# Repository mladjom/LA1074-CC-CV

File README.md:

# LT1074 Adjustable CV/CC Bench Power Supply

A buck-derived bench power supply built around the LT1074CT1 switching regulator, with adjustable output voltage and adjustable current limiting, plus a digital voltage/current readout.

## Overview

- **Topology:** LT1074CT1 buck converter
- **Voltage control:** Adjustable via potentiometer (RV1), feeding the LT1074's FB pin
- **Current control:** Adjustable fold-back current limit via an op-amp sense/compare loop, summed into the LT1074's VC (compensation) pin
- **Reference:** TL431-based VREF (2.5V), used by both the current-set pot and the current-sense op-amp
- **Readout:** DSN-VC288 digital voltmeter/ammeter module

## Main power stage

| Component | Function |
|---|---|
| U1 – LT1074CT1 | Buck regulator (VIN pin5, VSW pin4, FB pin1, VC pin2, GND pin3) |
| L1 | Buck inductor |
| D1 – MBR745 | Catch (freewheeling) diode |
| Cin1 | Input bulk capacitor (470µF) |
| COUT | Output bulk capacitor (470µF) |
| RV1 (5K) | Output voltage adjustment — sets FB divider ratio, adjusts VOUT |
| R2 (0.1Ω) | Current-sense shunt, in the ground return path |

**Output voltage** is set by RV1, which forms the feedback divider into the LT1074's FB pin (regulated against its internal ~2.21V reference). Turning RV1 sweeps VOUT from a few hundred mV up to close to VIN.

## Current-limit loop

| Component | Function |
|---|---|
| R2 (0.1Ω) | Current-sense shunt |
| U1A (LM358) | Difference amplifier — converts the voltage across R2 into a single-ended ISENSE signal (via R3/R4) |
| RV2 (10K) | Current setpoint (ISET), derived from VREF |
| U1B (LM358) | Compares ISENSE vs ISET, output = ICONTROL |
| R5 (1K) + clamp diode | Sums ICONTROL into the LT1074's VC pin |
| C3 (10nF) | Filtering on ICONTROL |

**How it works:** Under normal operation (load current below the ISET threshold), U1B's output (ICONTROL) sits high, well above VC's normal operating range. The clamp diode between R5 and VC is wired **anode toward VC, cathode toward R5/U1B**, so it stays reverse-biased and the current loop has no effect on regulation — the LT1074 is free to run pure CV mode.

If load current exceeds the ISET threshold, ISENSE rises above ISET, U1B's output swings low — below VC's level — forward-biasing the clamp diode. This lets U1B pull VC down through R5, reducing the LT1074's duty cycle and folding back the output voltage to hold current at the ISET limit. This is a standard current fold-back scheme, not a hard/foldback-free limiter — output voltage will sag as needed to keep current at the set point.

**Diode direction matters:** the opposite orientation (cathode toward VC) permanently forward-biases the diode any time ICONTROL idles high, jamming VC upward and preventing CV regulation entirely. If voltage ever "gets stuck near VIN and won't adjust," this is the first thing to check.

## Reference and setpoint

- **U2 (TL431LP) + R6 + C4** generate VREF (~2.5V), used as the reference rail for RV2 (current setpoint).
- **RV2 (10K)**, referenced to VREF and PGND, sets ISET — the current threshold at U1B's non-inverting input.

## Digital meter (DSN-VC288)

The module has 5 wires: thin red, thin black, yellow, thick red, thick black.

**Wiring (as built):**

| Wire | Connects to | Purpose |
|---|---|---|
| Thin red | VCC | Module power (+) |
| Thin black | **VOUT− node** (same point as thick black — not the general PGND bus) | Module power (−) / measurement reference |
| Yellow | VOUT+ | Voltage sense input |
| Thick red | Load negative terminal | Current path in |
| Thick black | VOUT− node (R2's load-side junction) | Current path out, through internal shunt (R018, 0.018Ω) |

**Current path order:** `VOUT+ → load → module thick red → internal shunt (R018) → module thick black → VOUT− → R2 (0.1Ω) → PGND`

R2 and the module's internal shunt are in series, so both should read the same current. This depends on thin black sharing the exact same node as thick black — if thin black is instead tied to the general PGND bus, current can bypass R2 through the module's internal ground connection and both R2 and the display will read incorrectly.

**Calibration:** The module has trim pots on the back (`V_ADJ`, `I_ADJ`) for fine calibration against a known reference. As built, current readout runs roughly 6–8% high across the tested range (0.85–1.29A vs. calculated actual) — within expected tolerance for this class of module, adjustable via `I_ADJ` if tighter accuracy is needed.

## Known limitations / notes

- Module power (30V max on all VC288 pins) — stay within that if this supply is ever run at a higher input voltage.
- The module's internal shunt (0.018Ω) adds a small amount of extra series resistance beyond R2 — negligible at low current, more noticeable near the 10A ceiling of the module.
- R2's current-sense node (used by the CC loop) is physically distinct from — but in series with — the meter's shunt. Both are valid current references; R2/U1A is what actually closes the CC loop, the VC288 is readout only.

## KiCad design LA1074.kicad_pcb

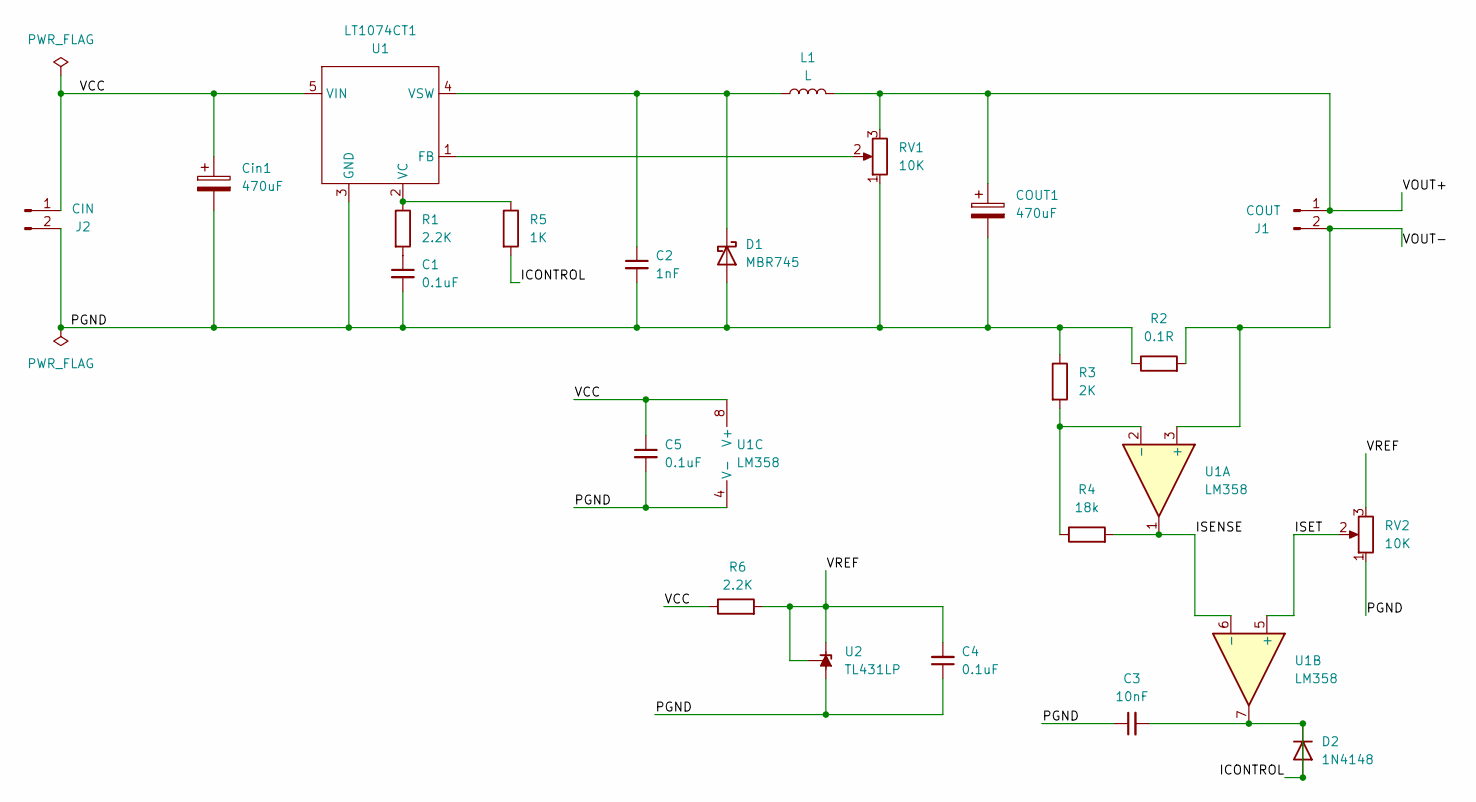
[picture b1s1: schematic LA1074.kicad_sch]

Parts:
C1, C4, C5: 0.1uF; C_Disc_D5.0mm_W2.5mm_P5.00mm
C2: 1nF; C_Disc_D5.0mm_W2.5mm_P5.00mm
C3: 10nF; C_Disc_D5.0mm_W2.5mm_P5.00mm
COUT1: 470uF; CP_Radial_D8.0mm_P3.50mm
Cin1: 470uF; CP_Radial_D8.0mm_P3.50mm
D1: MBR745; D_DO-41_SOD81_P10.16mm_Horizontal
D2: 1N4148; D_DO-35_SOD27_P7.62mm_Horizontal
J1: COUT; PinHeader_1x02_P2.54mm_Horizontal
J2: CIN; PinHeader_1x02_P2.54mm_Horizontal
L1: L; L_Axial_L20.0mm_D8.0mm_P25.40mm_Horizontal
LT1074CT1: U1; TO-220-5_Vertical
R1, R6: 2.2K; R_Axial_DIN0207_L6.3mm_D2.5mm_P7.62mm_Horizontal
R2: 0.1R; R_Axial_DIN0411_L9.9mm_D3.6mm_P12.70mm_Horizontal
R3: 2K; R_Axial_DIN0207_L6.3mm_D2.5mm_P7.62mm_Horizontal
R4: 18k; R_Axial_DIN0207_L6.3mm_D2.5mm_P7.62mm_Horizontal
R5: 1K; R_Axial_DIN0207_L6.3mm_D2.5mm_P7.62mm_Horizontal
RV1, RV2: 10K; PinSocket_1x03_P2.54mm_Vertical
U1: LM358; DIP-8_W7.62mm
U2: TL431LP; TO-92

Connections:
/ICONTROL: C3.2, D2.1 (K), D2.2 (A), R5.2, U1.7
/ISENSE: R4.2, U1.1, U1.6 (-)
/ISET: RV2.2, U1.5 (+)
/PGND: C1.2, C2.2, C3.1, C4.1, C5.2, COUT1.2, Cin1.2, D1.2 (A), J2.2, LT1074CT1.3 (GND), R2.1, R3.1, RV1.1, RV2.1, U1.4 (V-), U2.2 (A)
/VCC: C5.1, Cin1.1, J2.1, LT1074CT1.5 (VIN), R6.1, U1.8 (V+)
/VOUT+: COUT1.1, J1.1, L1.2, RV1.3
/VOUT-: J1.2, R2.2, U1.3 (+)
/VREF: C4.2, R6.2, RV2.3, U2.1 (REF), U2.3 (K)
unnamed: C1.1, R1.2
unnamed: C2.1, D1.1 (K), L1.1, LT1074CT1.4 (VSW)
unnamed: LT1074CT1.1 (FB), RV1.2
unnamed: LT1074CT1.2 (VC), R1.1, R5.1
unnamed: R3.2, R4.1, U1.2 (-)

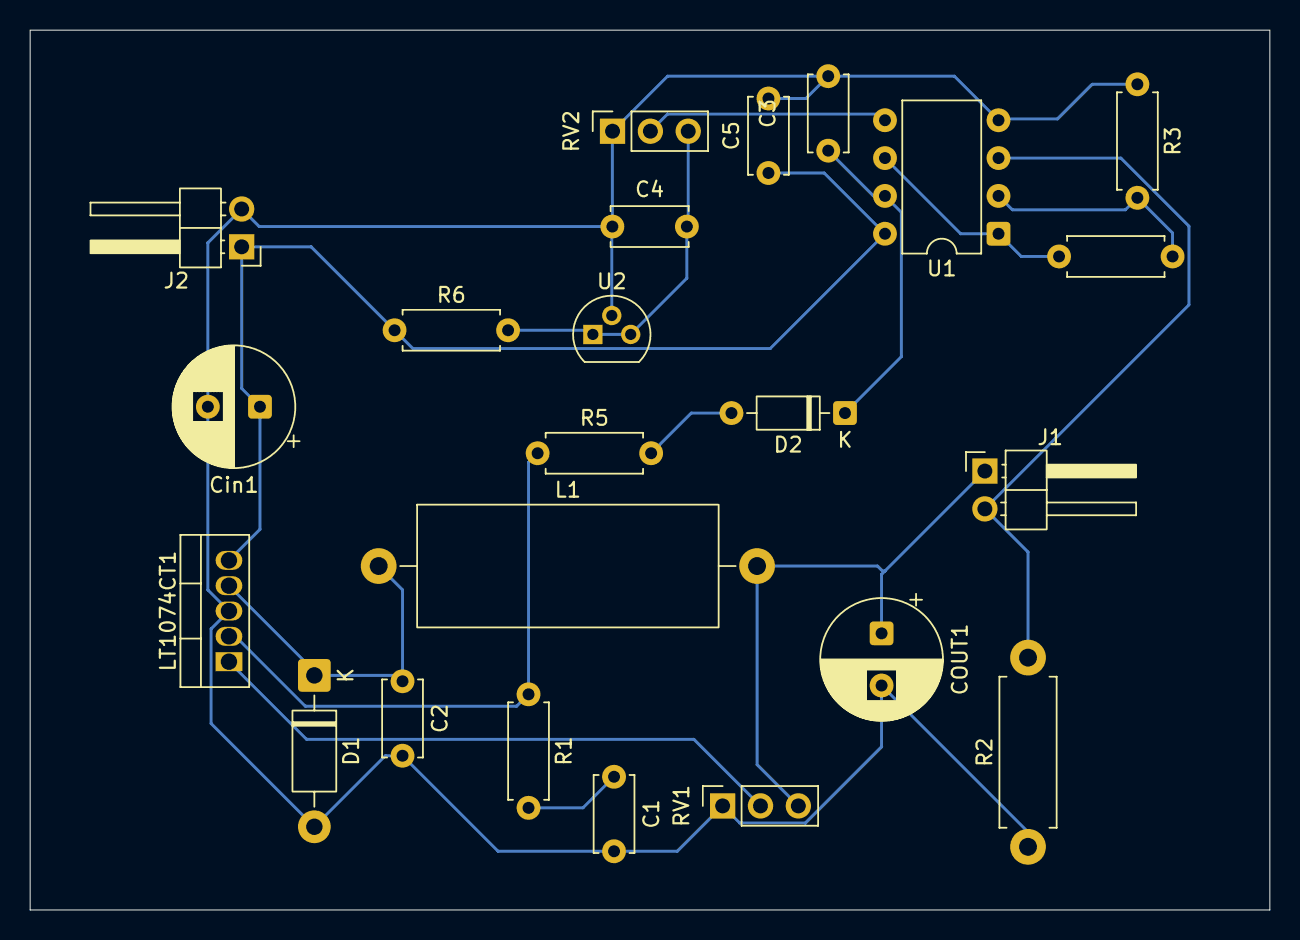
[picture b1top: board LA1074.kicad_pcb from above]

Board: 2 copper layers, 83.2 x 59.1 mm, 23 parts (0 on the bottom side), 13 nets.
